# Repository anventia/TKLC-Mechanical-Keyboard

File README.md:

# Tenkeyless-Compact
A Tenkeyless (TKL) Mechanical Keyboard, but more compact.
- PCB custom-made in KiCAD
- Support for:
  - Standard Cherry-style hotswappable switches
  - Gateron Low Profile hotswappable switches + Kailh Choc LP Stabilizers
- 3D printed plate + case 

[More images here](https://photos.anv3d.net/share/XmMfmQBNBfAzoucF3x74RvwrajWIMN9iaQ0uHyBkrugpA7lCPas15zOcdVT3Yqxft6Q)

Layout (from [Keyboard Layout Editor](http://www.keyboard-layout-editor.com/))

Libraries used: 
- https://github.com/sszczep/kicad-libraries
- https://github.com/Kriechi/kicad-library-WeAct-RP2040-Pico

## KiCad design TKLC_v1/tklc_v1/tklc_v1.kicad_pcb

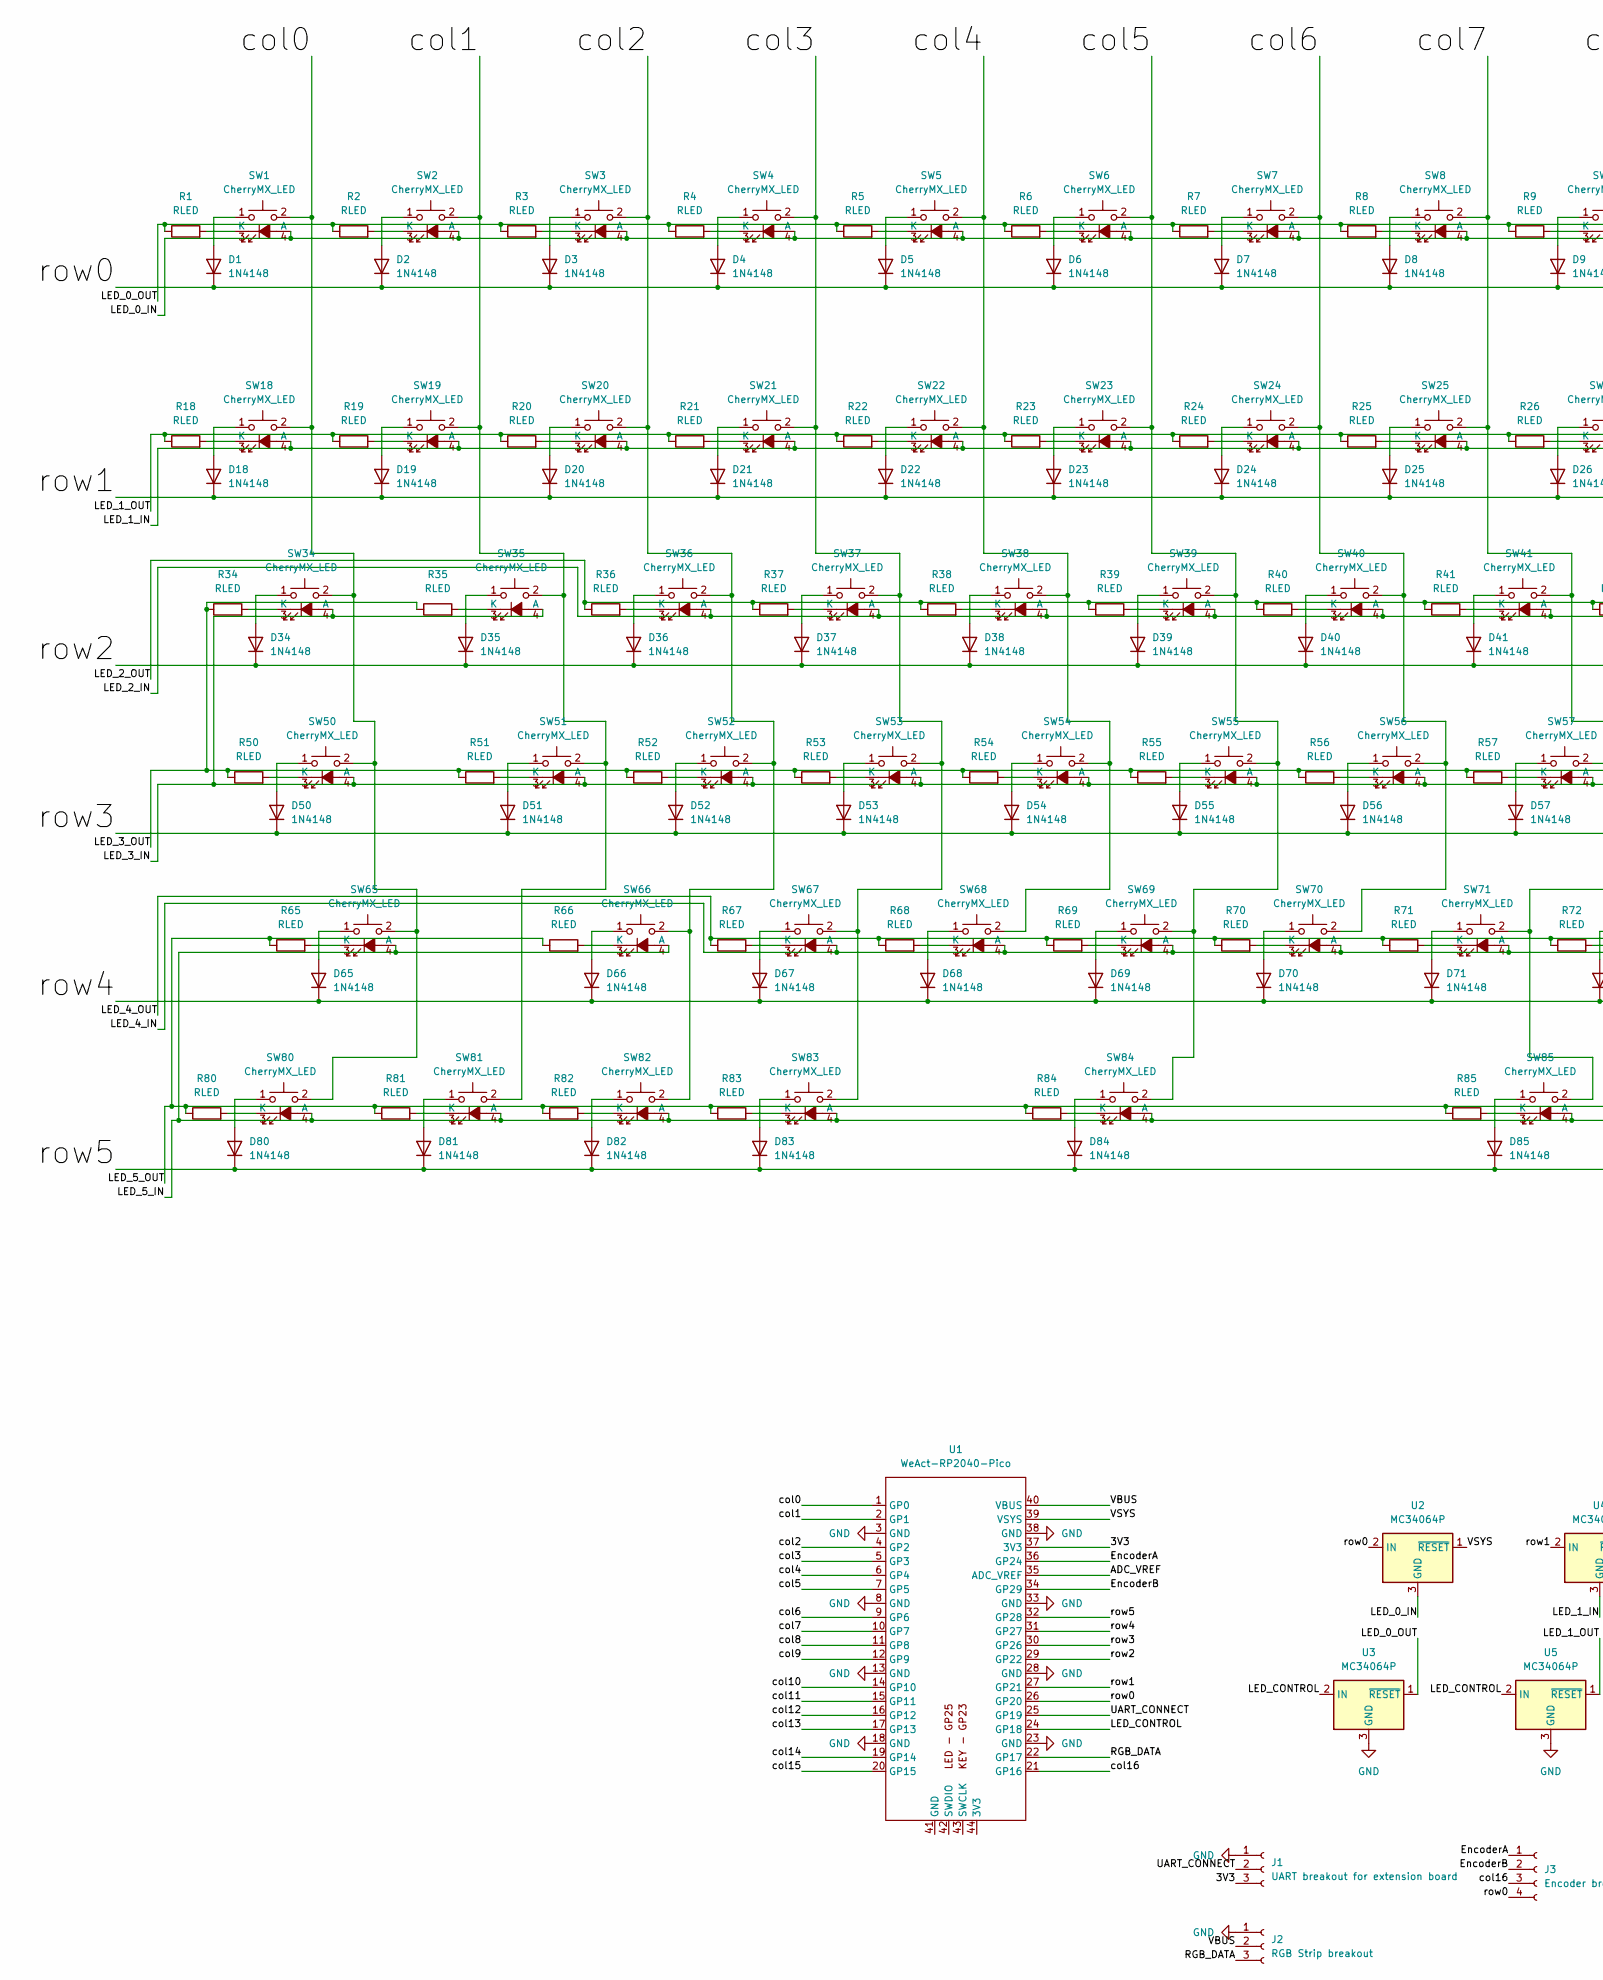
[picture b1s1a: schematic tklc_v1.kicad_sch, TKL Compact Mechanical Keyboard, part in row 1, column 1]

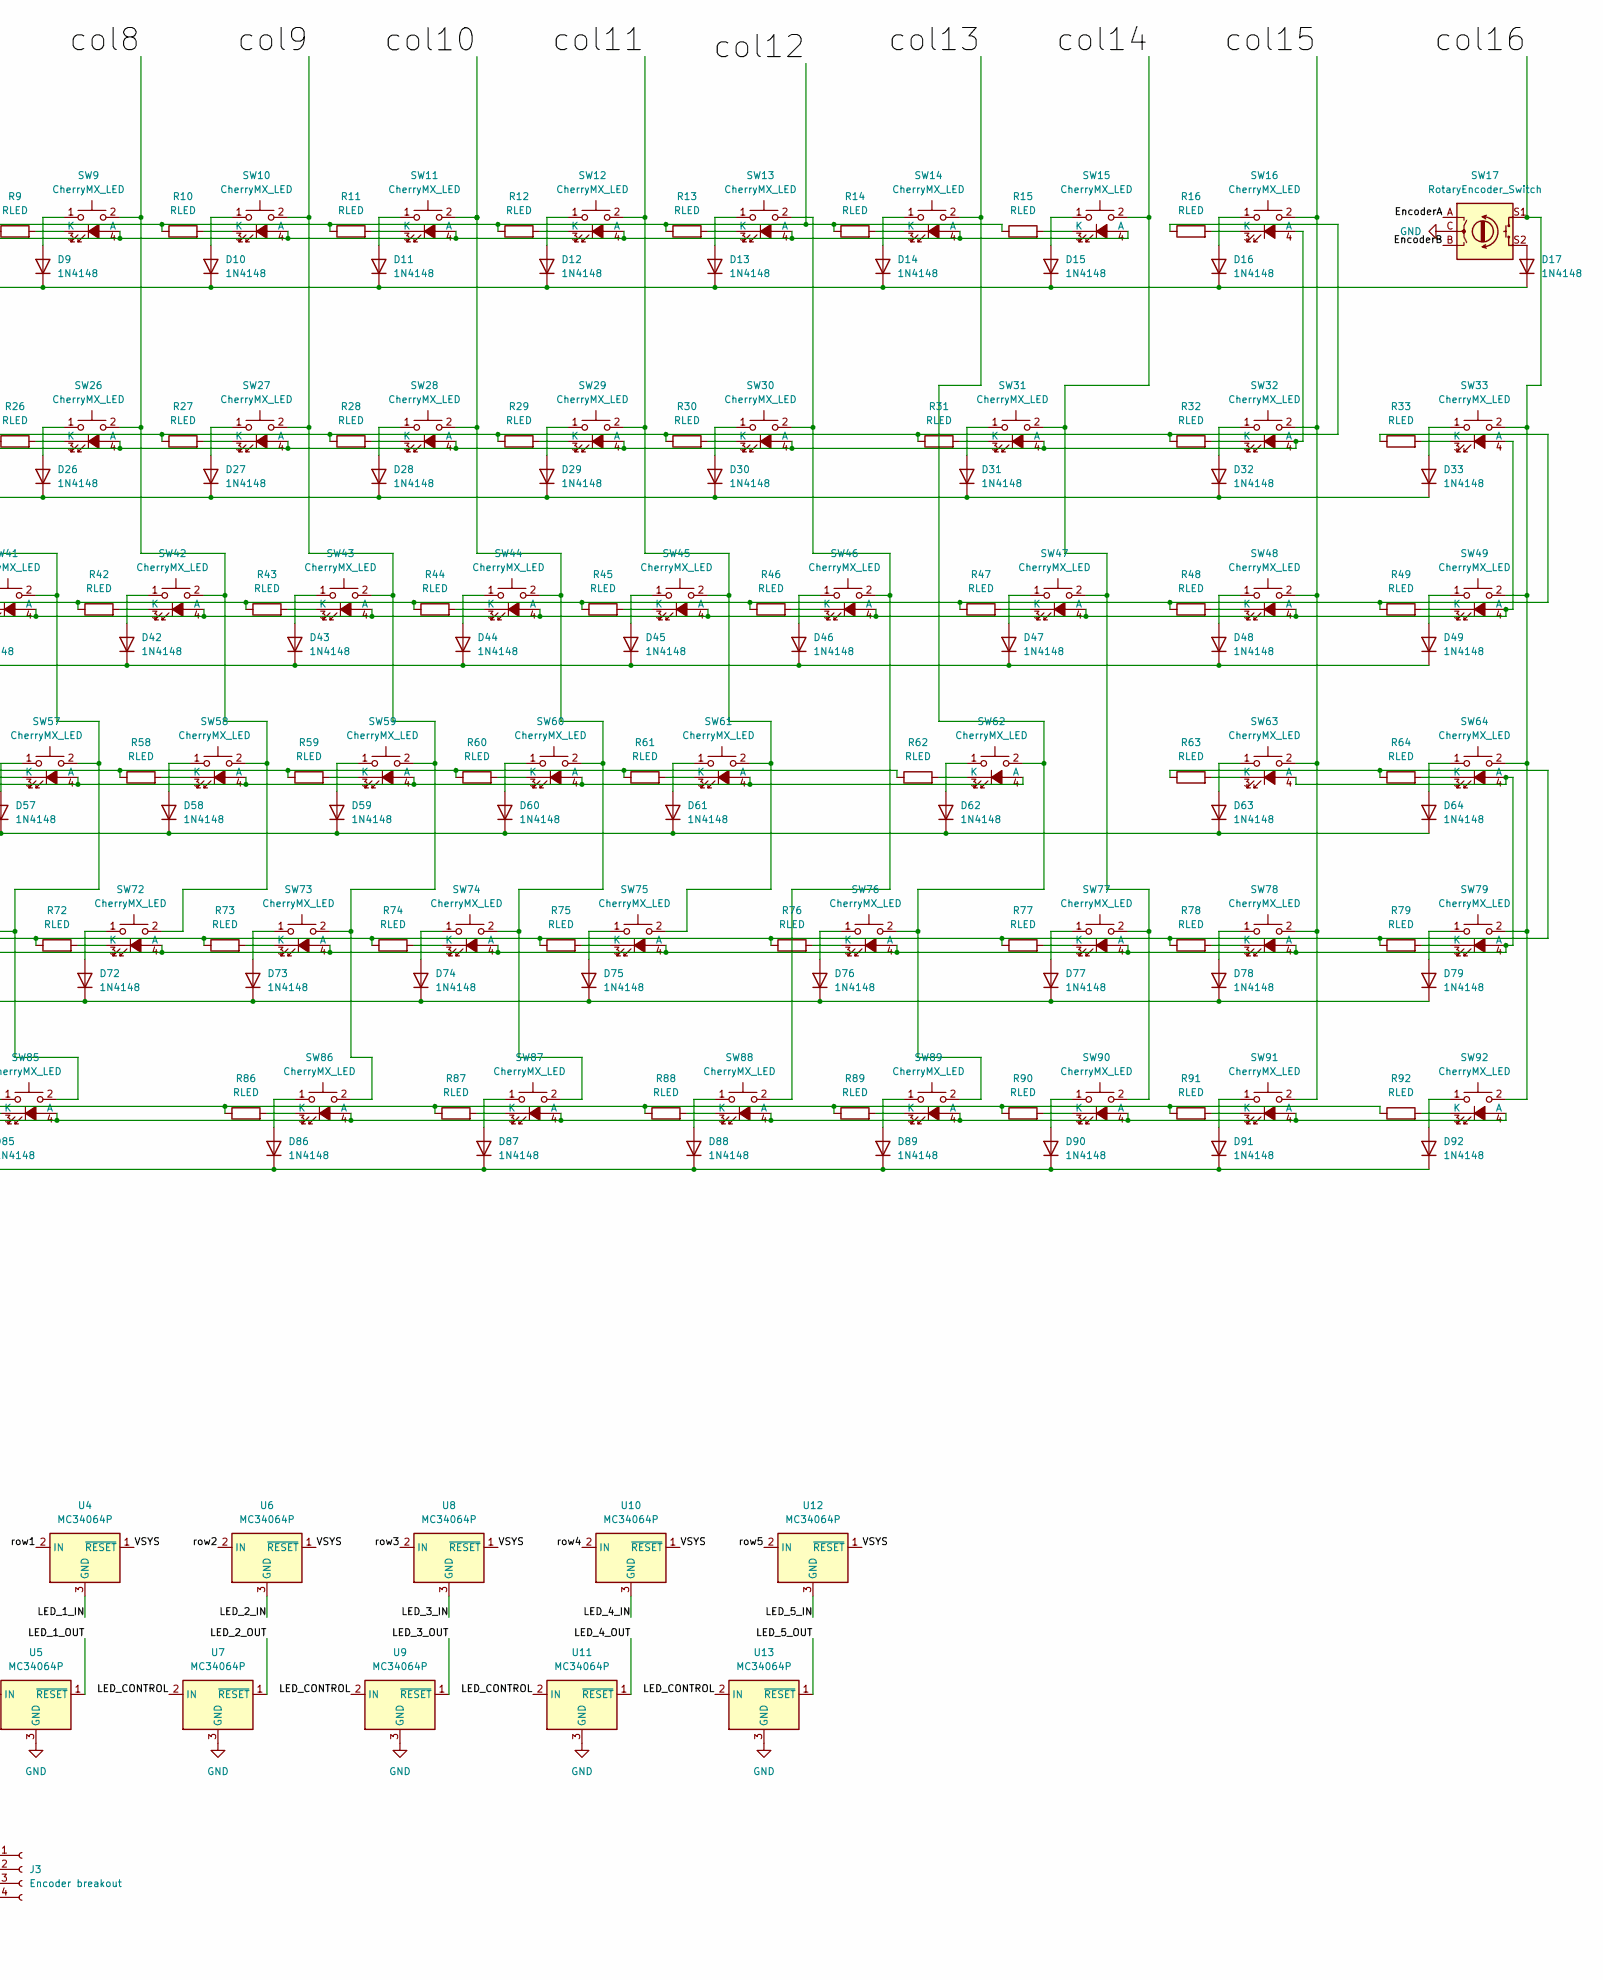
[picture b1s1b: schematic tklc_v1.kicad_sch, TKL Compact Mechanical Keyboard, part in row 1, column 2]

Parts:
D1, D2, D3, D4, D5, D6, D7, D8, D9, D10, D11, D12, D13, D14, D15, D16, D17, D18, D19, D20, D21, D22, D23, D24, D25, D26, D27, D28, D29, D30, D31, D32, D33, D34, D35, D36, D37, D38, D39, D40, D41, D42, D43, D44, D45, D46, D47, D48, D49, D50, D51, D52, D53, D54, D55, D56, D57, D58, D59, D60, D61, D62, D63, D64, D65, D66, D67, D68, D69, D70, D71, D72, D73, D74, D75, D76, D77, D78, D79, D80, D81, D82, D83, D84, D85, D86, D87, D88, D89, D90, D91, D92: 1N4148; D_DO-35_SOD27_P7.62mm_Horizontal
J1: UART breakout for extension board; FanPinHeader_1x03_P2.54mm_Vertical
J2: RGB Strip breakout; FanPinHeader_1x03_P2.54mm_Vertical
J3: Encoder breakout; FanPinHeader_1x04_P2.54mm_Vertical
R1, R2, R3, R4, R5, R6, R7, R8, R9, R10, R11, R12, R13, R14, R15, R16, R18, R19, R20, R21, R22, R23, R24, R25, R26, R27, R28, R29, R30, R31, R32, R33, R34, R35, R36, R37, R38, R39, R40, R41, R42, R43, R44, R45, R46, R47, R48, R49, R50, R51, R52, R53, R54, R55, R56, R57, R58, R59, R60, R61, R62, R63, R64, R65, R66, R67, R68, R69, R70, R71, R72, R73, R74, R75, R76, R77, R78, R79, R80, R81, R82, R83, R84, R85, R86, R87, R88, R89, R90, R91, R92: RLED; R_Axial_DIN0207_L6.3mEDIT_m_D2.5mm_P7.62mm_Horizontal
SW1, SW2, SW3, SW4, SW5, SW6, SW7, SW8, SW9, SW10, SW11, SW12, SW13, SW14, SW15, SW16, SW18, SW19, SW20, SW21, SW22, SW23, SW24, SW25, SW26, SW27, SW28, SW29, SW30, SW32, SW33, SW35, SW36, SW37, SW38, SW39, SW40, SW41, SW42, SW43, SW44, SW45, SW46, SW48, SW49, SW51, SW52, SW53, SW54, SW55, SW56, SW57, SW58, SW59, SW60, SW61, SW63, SW64, SW66, SW67, SW68, SW69, SW70, SW71, SW72, SW73, SW74, SW75, SW77, SW78, SW79, SW81, SW82, SW83, SW89, SW90, SW91, SW92: CherryMX_LED; CherryMX_1.00u_PCB_KailhSocket_LED
SW17: RotaryEncoder_Switch; EDIT_RotaryEncoder_Alps_EC11E-Switch_Vertical_H20mm
SW31: CherryMX_LED; CherryMX_2.00u_PCB_KailhSocket_StabWireTop_LED
SW34, SW47: CherryMX_LED; CherryMX_1.50u_PCB_KailhSocket_LED
SW50, SW76: CherryMX_LED; CherryMX_1.75u_PCB_KailhSocket_LED
SW62, SW65, SW85: CherryMX_LED; CherryMX_2.25u_PCB_KailhSocket_StabWireTop_LED
SW80, SW86, SW87, SW88: CherryMX_LED; CherryMX_1.25u_PCB_KailhSocket_LED
SW84: CherryMX_LED; CherryMX_2.75u_PCB_KailhSocket_StabWireTop_LED
U1: WeAct-RP2040-Pico
U2, U3, U4, U5, U6, U7, U8, U9, U10, U11, U12, U13: MC34064P; TO-92L_Inline

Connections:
/3V3: J1.3, U1.37 (3V3)
/ADC_VREF: U1.35 (ADC_VREF)
/EncoderA: J3.1, SW17.A, U1.36 (GP24)
/EncoderB: J3.2, SW17.B, U1.34 (GP29)
/LED_0_IN: SW1.4 (A), SW2.4 (A), SW3.4 (A), SW4.4 (A), SW5.4 (A), SW6.4 (A), SW7.4 (A), SW8.4 (A), SW9.4 (A), SW10.4 (A), SW11.4 (A), SW12.4 (A), SW13.4 (A), SW14.4 (A), SW15.4 (A), U2.3 (GND)
/LED_0_OUT: R1.1, R2.1, R3.1, R4.1, R5.1, R6.1, R7.1, R8.1, R9.1, R10.1, R11.1, R12.1, R13.1, R14.1, R15.1, U1.16 (GP12), U3.1 (~RESET)
/LED_1_IN: SW16.4 (A), SW18.4 (A), SW19.4 (A), SW20.4 (A), SW21.4 (A), SW22.4 (A), SW23.4 (A), SW24.4 (A), SW25.4 (A), SW26.4 (A), SW27.4 (A), SW28.4 (A), SW29.4 (A), SW30.4 (A), SW31.4 (A), SW32.4 (A), U4.3 (GND)
/LED_1_OUT: R16.1, R18.1, R19.1, R20.1, R21.1, R22.1, R23.1, R24.1, R25.1, R26.1, R27.1, R28.1, R29.1, R30.1, R31.1, R32.1, U5.1 (~RESET)
/LED_2_IN: SW33.4 (A), SW36.4 (A), SW37.4 (A), SW38.4 (A), SW39.4 (A), SW40.4 (A), SW41.4 (A), SW42.4 (A), SW43.4 (A), SW44.4 (A), SW45.4 (A), SW46.4 (A), SW47.4 (A), SW48.4 (A), SW49.4 (A), U6.3 (GND)
/LED_2_OUT: R33.1, R36.1, R37.1, R38.1, R39.1, R40.1, R41.1, R42.1, R43.1, R44.1, R45.1, R46.1, R47.1, R48.1, R49.1, U7.1 (~RESET)
/LED_3_IN: SW34.4 (A), SW35.4 (A), SW50.4 (A), SW51.4 (A), SW52.4 (A), SW53.4 (A), SW54.4 (A), SW55.4 (A), SW56.4 (A), SW57.4 (A), SW58.4 (A), SW59.4 (A), SW60.4 (A), SW61.4 (A), SW62.4 (A), U8.3 (GND)
/LED_3_OUT: R34.1, R35.1, R50.1, R51.1, R52.1, R53.1, R54.1, R55.1, R56.1, R57.1, R58.1, R59.1, R60.1, R61.1, R62.1, U9.1 (~RESET)
/LED_4_IN: SW63.4 (A), SW64.4 (A), SW67.4 (A), SW68.4 (A), SW69.4 (A), SW70.4 (A), SW71.4 (A), SW72.4 (A), SW73.4 (A), SW74.4 (A), SW75.4 (A), SW76.4 (A), SW77.4 (A), SW78.4 (A), SW79.4 (A), U10.3 (GND)
/LED_4_OUT: R63.1, R64.1, R67.1, R68.1, R69.1, R70.1, R71.1, R72.1, R73.1, R74.1, R75.1, R76.1, R77.1, R78.1, R79.1, U11.1 (~RESET)
/LED_5_IN: SW65.4 (A), SW66.4 (A), SW80.4 (A), SW81.4 (A), SW82.4 (A), SW83.4 (A), SW84.4 (A), SW85.4 (A), SW86.4 (A), SW87.4 (A), SW88.4 (A), SW89.4 (A), SW90.4 (A), SW91.4 (A), SW92.4 (A), U12.3 (GND)
/LED_5_OUT: R65.1, R66.1, R80.1, R81.1, R82.1, R83.1, R84.1, R85.1, R86.1, R87.1, R88.1, R89.1, R90.1, R91.1, R92.1, U13.1 (~RESET)
/LED_CONTROL: U1.24 (GP18), U3.2 (IN), U5.2 (IN), U7.2 (IN), U9.2 (IN), U11.2 (IN), U13.2 (IN)
/RGB_DATA: J2.3, U1.22 (GP17)
/UART_CONNECT: J1.2, U1.25 (GP19)
/VBUS: J2.2, U1.40 (VBUS)
/VSYS: U1.39 (VSYS), U2.1 (~RESET), U4.1 (~RESET), U6.1 (~RESET), U8.1 (~RESET), U10.1 (~RESET), U12.1 (~RESET)
/col0: SW1.2, SW18.2, SW34.2, SW50.2, SW65.2, SW80.2, U1.1 (GP0)
/col1: SW2.2, SW19.2, SW35.2, SW51.2, SW81.2, U1.2 (GP1)
/col2: SW3.2, SW20.2, SW36.2, SW52.2, SW66.2, SW82.2, U1.4 (GP2)
/col3: SW4.2, SW21.2, SW37.2, SW53.2, SW67.2, SW83.2, U1.5 (GP3)
/col4: SW5.2, SW22.2, SW38.2, SW54.2, SW68.2, U1.6 (GP4)
/col5: SW6.2, SW23.2, SW39.2, SW55.2, SW69.2, SW84.2, U1.7 (GP5)
/col6: SW7.2, SW24.2, SW40.2, SW56.2, SW70.2, U1.9 (GP6)
/col7: SW8.2, SW25.2, SW41.2, SW57.2, SW71.2, SW85.2, U1.10 (GP7)
/col8: SW9.2, SW26.2, SW42.2, SW58.2, SW72.2, U1.11 (GP8)
/col9: SW10.2, SW27.2, SW43.2, SW59.2, SW73.2, SW86.2, U1.12 (GP9)
/col10: SW11.2, SW28.2, SW44.2, SW60.2, SW74.2, SW87.2, U1.14 (GP10)
/col11: SW12.2, SW29.2, SW45.2, SW61.2, SW75.2, U1.15 (GP11)
/col13: SW14.2, SW62.2, SW76.2, SW89.2, U1.17 (GP13)
/col14: SW15.2, SW31.2, SW47.2, SW77.2, SW90.2, U1.19 (GP14)
/col15: SW16.2, SW32.2, SW48.2, SW63.2, SW78.2, SW91.2, U1.20 (GP15)
/col16: J3.3, SW17.S1, SW33.2, SW49.2, SW64.2, SW79.2, SW92.2, U1.21 (GP16)
/row0: D1.1 (K), D2.1 (K), D3.1 (K), D4.1 (K), D5.1 (K), D6.1 (K), D7.1 (K), D8.1 (K), D9.1 (K), D10.1 (K), D11.1 (K), D12.1 (K), D13.1 (K), D14.1 (K), D15.1 (K), D16.1 (K), D17.1 (K), J3.4, U1.26 (GP20), U2.2 (IN)
/row1: D18.1 (K), D19.1 (K), D20.1 (K), D21.1 (K), D22.1 (K), D23.1 (K), D24.1 (K), D25.1 (K), D26.1 (K), D27.1 (K), D28.1 (K), D29.1 (K), D30.1 (K), D31.1 (K), D32.1 (K), D33.1 (K), U1.27 (GP21), U4.2 (IN)
/row2: D34.1 (K), D35.1 (K), D36.1 (K), D37.1 (K), D38.1 (K), D39.1 (K), D40.1 (K), D41.1 (K), D42.1 (K), D43.1 (K), D44.1 (K), D45.1 (K), D46.1 (K), D47.1 (K), D48.1 (K), D49.1 (K), U1.29 (GP22), U6.2 (IN)
/row3: D50.1 (K), D51.1 (K), D52.1 (K), D53.1 (K), D54.1 (K), D55.1 (K), D56.1 (K), D57.1 (K), D58.1 (K), D59.1 (K), D60.1 (K), D61.1 (K), D62.1 (K), D63.1 (K), D64.1 (K), U1.30 (GP26), U8.2 (IN)
/row4: D65.1 (K), D66.1 (K), D67.1 (K), D68.1 (K), D69.1 (K), D70.1 (K), D71.1 (K), D72.1 (K), D73.1 (K), D74.1 (K), D75.1 (K), D76.1 (K), D77.1 (K), D78.1 (K), D79.1 (K), U1.31 (GP27), U10.2 (IN)
/row5: D80.1 (K), D81.1 (K), D82.1 (K), D83.1 (K), D84.1 (K), D85.1 (K), D86.1 (K), D87.1 (K), D88.1 (K), D89.1 (K), D90.1 (K), D91.1 (K), D92.1 (K), U1.32 (GP28), U12.2 (IN)
GND: J1.1, J2.1, SW17.C, U1.3 (GND), U1.8 (GND), U1.13 (GND), U1.18 (GND), U1.23 (GND), U1.28 (GND), U1.33 (GND), U1.38 (GND), U3.3 (GND), U5.3 (GND), U7.3 (GND), U9.3 (GND), U11.3 (GND), U13.3 (GND)
unnamed: D1.2 (A), SW1.1
unnamed: D2.2 (A), SW2.1
unnamed: D3.2 (A), SW3.1
unnamed: D4.2 (A), SW4.1
unnamed: D5.2 (A), SW5.1
unnamed: D6.2 (A), SW6.1
unnamed: D7.2 (A), SW7.1
unnamed: D8.2 (A), SW8.1
unnamed: D9.2 (A), SW9.1
unnamed: D10.2 (A), SW10.1
unnamed: D11.2 (A), SW11.1
unnamed: D12.2 (A), SW12.1
unnamed: D13.2 (A), SW13.1
unnamed: D14.2 (A), SW14.1
unnamed: D15.2 (A), SW15.1
unnamed: D16.2 (A), SW16.1
unnamed: D17.2 (A), SW17.S2
unnamed: D18.2 (A), SW18.1
unnamed: D19.2 (A), SW19.1
unnamed: D20.2 (A), SW20.1
unnamed: D21.2 (A), SW21.1
unnamed: D22.2 (A), SW22.1
unnamed: D23.2 (A), SW23.1
unnamed: D24.2 (A), SW24.1
unnamed: D25.2 (A), SW25.1
unnamed: D26.2 (A), SW26.1
unnamed: D27.2 (A), SW27.1
unnamed: D28.2 (A), SW28.1
unnamed: D29.2 (A), SW29.1
unnamed: D30.2 (A), SW30.1
unnamed: D31.2 (A), SW31.1
unnamed: D32.2 (A), SW32.1
unnamed: D33.2 (A), SW33.1
unnamed: D34.2 (A), SW34.1
unnamed: D35.2 (A), SW35.1
unnamed: D36.2 (A), SW36.1
unnamed: D37.2 (A), SW37.1
unnamed: D38.2 (A), SW38.1
unnamed: D39.2 (A), SW39.1
unnamed: D40.2 (A), SW40.1
unnamed: D41.2 (A), SW41.1
unnamed: D42.2 (A), SW42.1
unnamed: D43.2 (A), SW43.1
unnamed: D44.2 (A), SW44.1
unnamed: D45.2 (A), SW45.1
unnamed: D46.2 (A), SW46.1
unnamed: D47.2 (A), SW47.1
unnamed: D48.2 (A), SW48.1
unnamed: D49.2 (A), SW49.1
unnamed: D50.2 (A), SW50.1
unnamed: D51.2 (A), SW51.1
unnamed: D52.2 (A), SW52.1
unnamed: D53.2 (A), SW53.1
unnamed: D54.2 (A), SW54.1
unnamed: D55.2 (A), SW55.1
unnamed: D56.2 (A), SW56.1
unnamed: D57.2 (A), SW57.1
unnamed: D58.2 (A), SW58.1
unnamed: D59.2 (A), SW59.1
unnamed: D60.2 (A), SW60.1
unnamed: D61.2 (A), SW61.1
unnamed: D62.2 (A), SW62.1
unnamed: D63.2 (A), SW63.1
unnamed: D64.2 (A), SW64.1
unnamed: D65.2 (A), SW65.1
unnamed: D66.2 (A), SW66.1
unnamed: D67.2 (A), SW67.1
unnamed: D68.2 (A), SW68.1
unnamed: D69.2 (A), SW69.1
unnamed: D70.2 (A), SW70.1
unnamed: D71.2 (A), SW71.1
unnamed: D72.2 (A), SW72.1
unnamed: D73.2 (A), SW73.1
unnamed: D74.2 (A), SW74.1
unnamed: D75.2 (A), SW75.1
unnamed: D76.2 (A), SW76.1
unnamed: D77.2 (A), SW77.1
unnamed: D78.2 (A), SW78.1
unnamed: D79.2 (A), SW79.1
unnamed: D80.2 (A), SW80.1
unnamed: D81.2 (A), SW81.1
unnamed: D82.2 (A), SW82.1
unnamed: D83.2 (A), SW83.1
unnamed: D84.2 (A), SW84.1
unnamed: D85.2 (A), SW85.1
unnamed: D86.2 (A), SW86.1
unnamed: D87.2 (A), SW87.1
unnamed: D88.2 (A), SW88.1
unnamed: D89.2 (A), SW89.1
unnamed: D90.2 (A), SW90.1
unnamed: D91.2 (A), SW91.1
unnamed: D92.2 (A), SW92.1
unnamed: R1.2, SW1.3 (K)
unnamed: R2.2, SW2.3 (K)
unnamed: R3.2, SW3.3 (K)
unnamed: R4.2, SW4.3 (K)
unnamed: R5.2, SW5.3 (K)
unnamed: R6.2, SW6.3 (K)
unnamed: R7.2, SW7.3 (K)
unnamed: R8.2, SW8.3 (K)
unnamed: R9.2, SW9.3 (K)
unnamed: R10.2, SW10.3 (K)
unnamed: R11.2, SW11.3 (K)
unnamed: R12.2, SW12.3 (K)
unnamed: R13.2, SW13.3 (K)
unnamed: R14.2, SW14.3 (K)
unnamed: R15.2, SW15.3 (K)
unnamed: R16.2, SW16.3 (K)
unnamed: R18.2, SW18.3 (K)
unnamed: R19.2, SW19.3 (K)
unnamed: R20.2, SW20.3 (K)
unnamed: R21.2, SW21.3 (K)
unnamed: R22.2, SW22.3 (K)
unnamed: R23.2, SW23.3 (K)
unnamed: R24.2, SW24.3 (K)
unnamed: R25.2, SW25.3 (K)
unnamed: R26.2, SW26.3 (K)
unnamed: R27.2, SW27.3 (K)
unnamed: R28.2, SW28.3 (K)
unnamed: R29.2, SW29.3 (K)
unnamed: R30.2, SW30.3 (K)
unnamed: R31.2, SW31.3 (K)
unnamed: R32.2, SW32.3 (K)
unnamed: R33.2, SW33.3 (K)
unnamed: R34.2, SW34.3 (K)
unnamed: R35.2, SW35.3 (K)
unnamed: R36.2, SW36.3 (K)
unnamed: R37.2, SW37.3 (K)
unnamed: R38.2, SW38.3 (K)
unnamed: R39.2, SW39.3 (K)
unnamed: R40.2, SW40.3 (K)
unnamed: R41.2, SW41.3 (K)
unnamed: R42.2, SW42.3 (K)
unnamed: R43.2, SW43.3 (K)
unnamed: R44.2, SW44.3 (K)
unnamed: R45.2, SW45.3 (K)
unnamed: R46.2, SW46.3 (K)
unnamed: R47.2, SW47.3 (K)
unnamed: R48.2, SW48.3 (K)
unnamed: R49.2, SW49.3 (K)
unnamed: R50.2, SW50.3 (K)
unnamed: R51.2, SW51.3 (K)
unnamed: R52.2, SW52.3 (K)
unnamed: R53.2, SW53.3 (K)
unnamed: R54.2, SW54.3 (K)
unnamed: R55.2, SW55.3 (K)
unnamed: R56.2, SW56.3 (K)
unnamed: R57.2, SW57.3 (K)
unnamed: R58.2, SW58.3 (K)
unnamed: R59.2, SW59.3 (K)
unnamed: R60.2, SW60.3 (K)
unnamed: R61.2, SW61.3 (K)
unnamed: R62.2, SW62.3 (K)
unnamed: R63.2, SW63.3 (K)
unnamed: R64.2, SW64.3 (K)
unnamed: R65.2, SW65.3 (K)
unnamed: R66.2, SW66.3 (K)
unnamed: R67.2, SW67.3 (K)
unnamed: R68.2, SW68.3 (K)
unnamed: R69.2, SW69.3 (K)
unnamed: R70.2, SW70.3 (K)
unnamed: R71.2, SW71.3 (K)
unnamed: R72.2, SW72.3 (K)
unnamed: R73.2, SW73.3 (K)
unnamed: R74.2, SW74.3 (K)
unnamed: R75.2, SW75.3 (K)
unnamed: R76.2, SW76.3 (K)
unnamed: R77.2, SW77.3 (K)
unnamed: R78.2, SW78.3 (K)
unnamed: R79.2, SW79.3 (K)
unnamed: R80.2, SW80.3 (K)
unnamed: R81.2, SW81.3 (K)
unnamed: R82.2, SW82.3 (K)
unnamed: R83.2, SW83.3 (K)
unnamed: R84.2, SW84.3 (K)
unnamed: R85.2, SW85.3 (K)
unnamed: R86.2, SW86.3 (K)
unnamed: R87.2, SW87.3 (K)
unnamed: R88.2, SW88.3 (K)
unnamed: R89.2, SW89.3 (K)
unnamed: R90.2, SW90.3 (K)
unnamed: R91.2, SW91.3 (K)
unnamed: R92.2, SW92.3 (K)
unnamed: SW13.2, SW30.2, SW46.2, SW88.2

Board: 2 copper layers, 291 parts (0 on the bottom side), 227 nets, no tracks yet.

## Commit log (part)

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2022-08-03 Finished laying out PCB
2022-08-04 Changed resistor layout
2022-08-04 Rows and columns finished wiring
    Removed LED wiring, may switch to RGB
2022-08-05 Added SK6812 LEDs to schematic
2022-08-05 Restructure versions
2022-08-15 Started Low Profile ver
2022-08-18 Finished wiring LEDs and Matrix to each other
2022-08-19 Rename TKLC_v1/tklc_v1_rgb_LP/test.txt to TKLC_v1/tklc_v1_rgb/test.txt
2022-08-19 renaming stuff
2022-08-19 this dir used to be called LP, but is now renamed
2022-08-19 Wired columns
2022-08-20 Finished wiring everything but LED Power
2022-08-20 FINISHED! Just need finishing touches
    need to do rotary encoder button, art, and add teardrops and rounded corners.
2022-08-20 Finished rounding everything
2022-08-21 Started adding art/labels
2022-08-22 Finished art, added mounting holes and teardrops.
2022-08-28 Generated Gerber files and ordered PCBs
2022-08-29 Fixed problem with tracks too close to edge cuts
2026-06-30 add image to README
    Added an image and layout information to the README.
